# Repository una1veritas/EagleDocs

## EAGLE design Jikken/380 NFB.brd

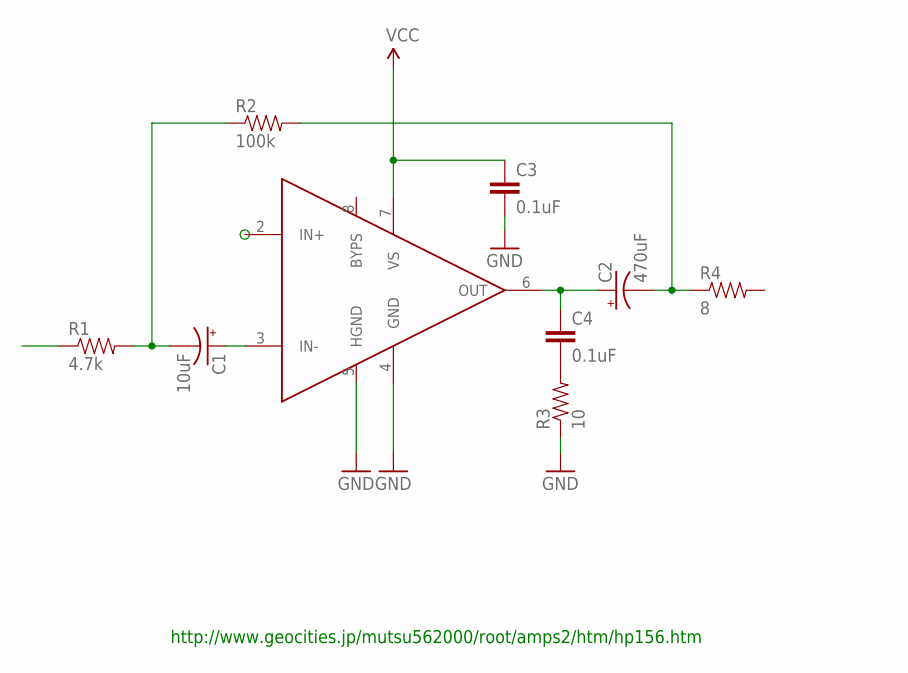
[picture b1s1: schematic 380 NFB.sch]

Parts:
C1: 10uF; CPOL-RADIAL-100UF-25V
C2: 470uF; CPOL-RADIAL-1000UF-25V
C3, C4: 0.1uF; CAP-PTH-SMALL-KIT
R1: 4.7k; AXIAL-0.3
R2: 100k; AXIAL-0.3
R3: 10; AXIAL-0.3
R4: 8; AXIAL-0.3
U$1: LM380N-8; DIL08

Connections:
GND: C3.2, R3.P$1 (1), U$1.4 (GND), U$1.5 (HGND)
unnamed: C1.1 (+), U$1.3 (IN-)
unnamed: C1.2 (-), R1.P$2 (2), R2.P$1 (1)
unnamed: C2.2 (-), R2.P$2 (2), R4.P$1 (1)
unnamed: C2.1 (+), C4.1, U$1.6 (OUT)
unnamed: C4.2, R3.P$2 (2)
VCC: C3.1, U$1.7 (VS)

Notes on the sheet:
http://www.geocities.jp/mutsu562000/root/amps2/htm/hp156.htm

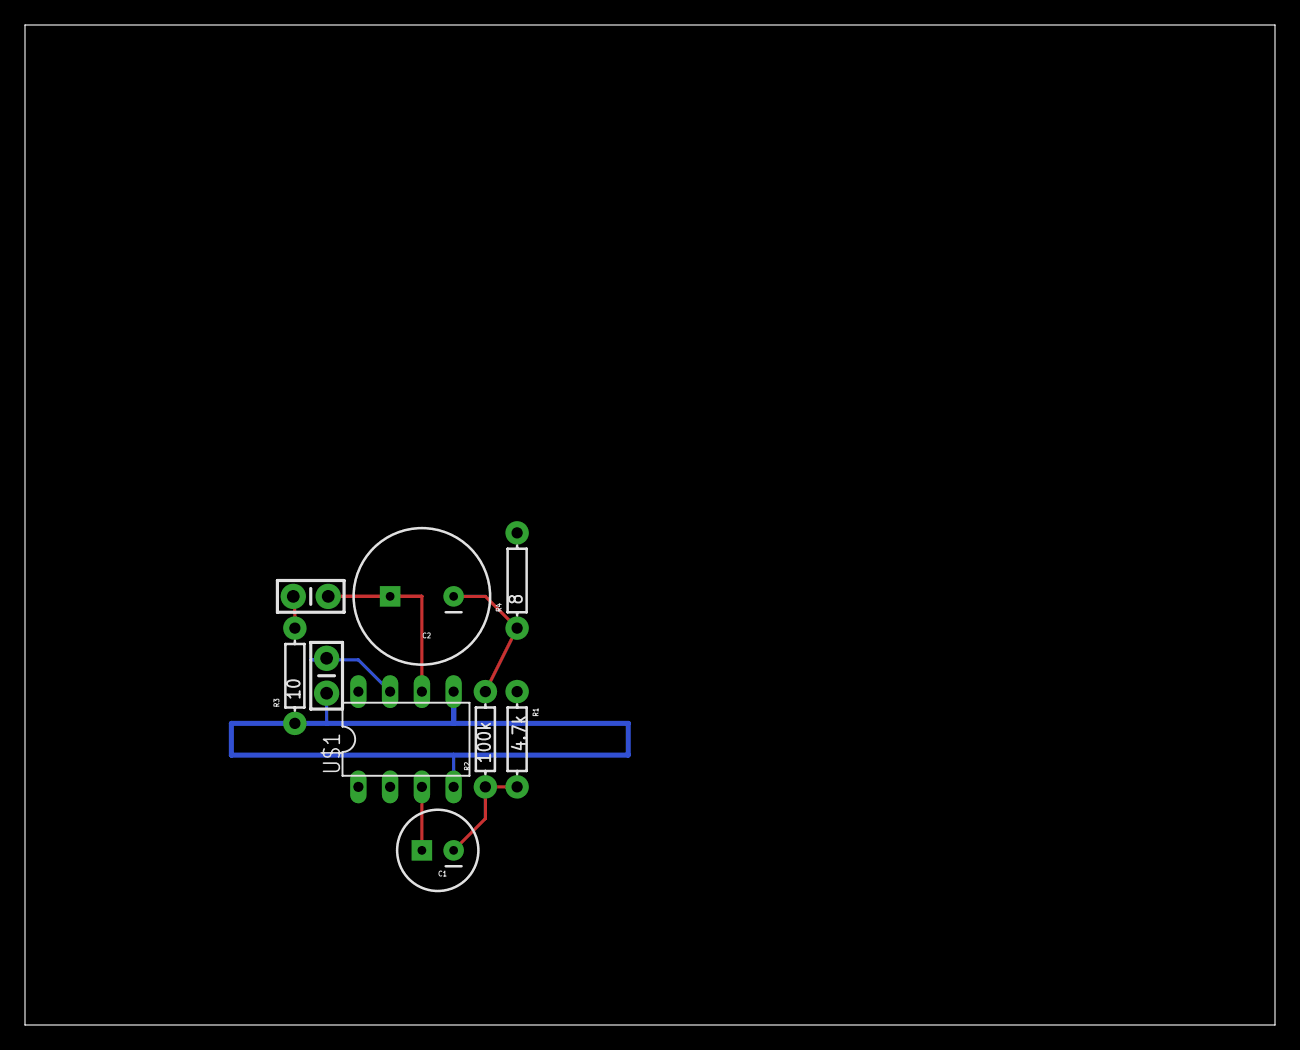
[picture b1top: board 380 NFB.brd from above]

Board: 2 copper layers, 100.0 x 80.0 mm, 9 parts (0 on the bottom side), 7 nets.

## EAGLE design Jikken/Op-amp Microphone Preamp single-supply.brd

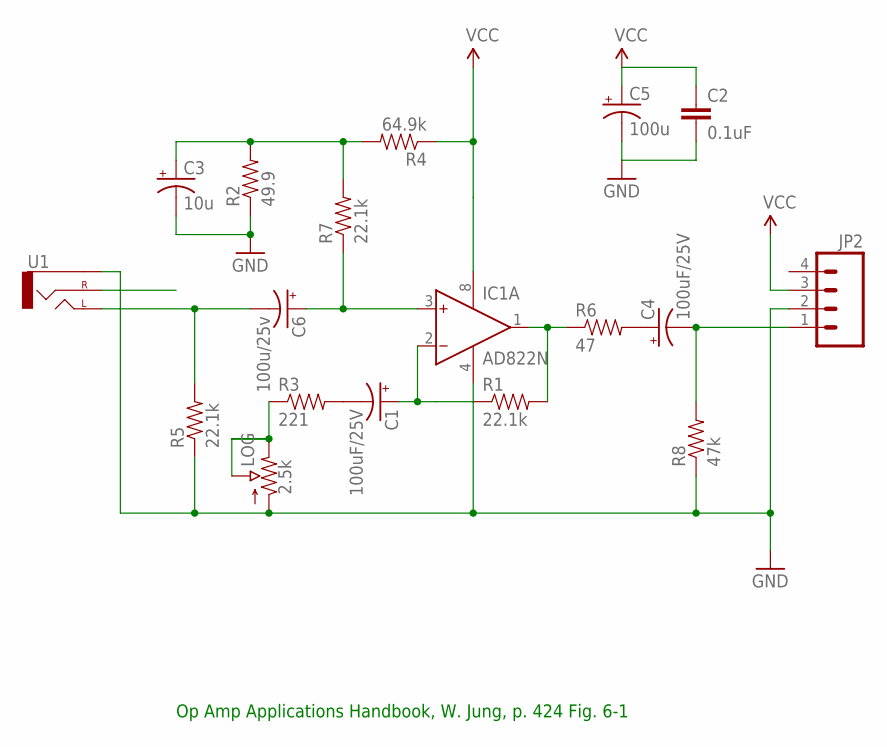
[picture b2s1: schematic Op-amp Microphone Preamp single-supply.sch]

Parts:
C1, C4: 100uF/25V; CPOL-RADIAL-100UF-25V
C2: 0.1uF; CAP-PTH-SMALL-KIT
C3: 10u; CPOL-RADIAL-100UF-25V
C5: 100u; CPOL-RADIAL-100UF-25V
C6: 100u/25v; CPOL-RADIAL-100UF-25V
IC1: AD822N; DIL08
JP2: M04POLAR; MOLEX-1X4
LOG: 2.5k; POT_ALPHA_RV16AF-20
R1, R5, R7: 22.1k; 1/6W-RES
R2: 49.9; 1/6W-RES
R3: 221; 1/6W-RES
R4: 64.9k; 1/6W-RES
R6: 47; 1/6W-RES
R8: 47k; 1/6W-RES
U1: AUDIO-JACKPTH; AUDIO-JACK

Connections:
GND: C2.2, C3.2 (-), C5.2 (-), IC1.4 (V-), JP2.2, LOG.1 (A), R2.1, R5.1, R8.1, U1.SLEEVE
unnamed: C3.1 (+), R2.2, R4.2, R7.2
unnamed: C1.2 (-), R3.2
unnamed: IC1.1 (OUT), R1.2, R6.1
unnamed: LOG.2 (S), LOG.3 (E), R3.1
unnamed: C1.1 (+), IC1.2 (IN-), R1.1
unnamed: C6.1 (+), IC1.3 (IN+), R7.1
unnamed: C4.1 (+), R6.2
unnamed: C6.2 (-), R5.2, U1.TIP (LEFT)
unnamed: C4.2 (-), JP2.1, R8.2
VCC: C2.1, C5.1 (+), IC1.8 (V+), JP2.3, R4.1

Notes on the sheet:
Op Amp Applications Handbook, W. Jung, p. 424 Fig. 6-1

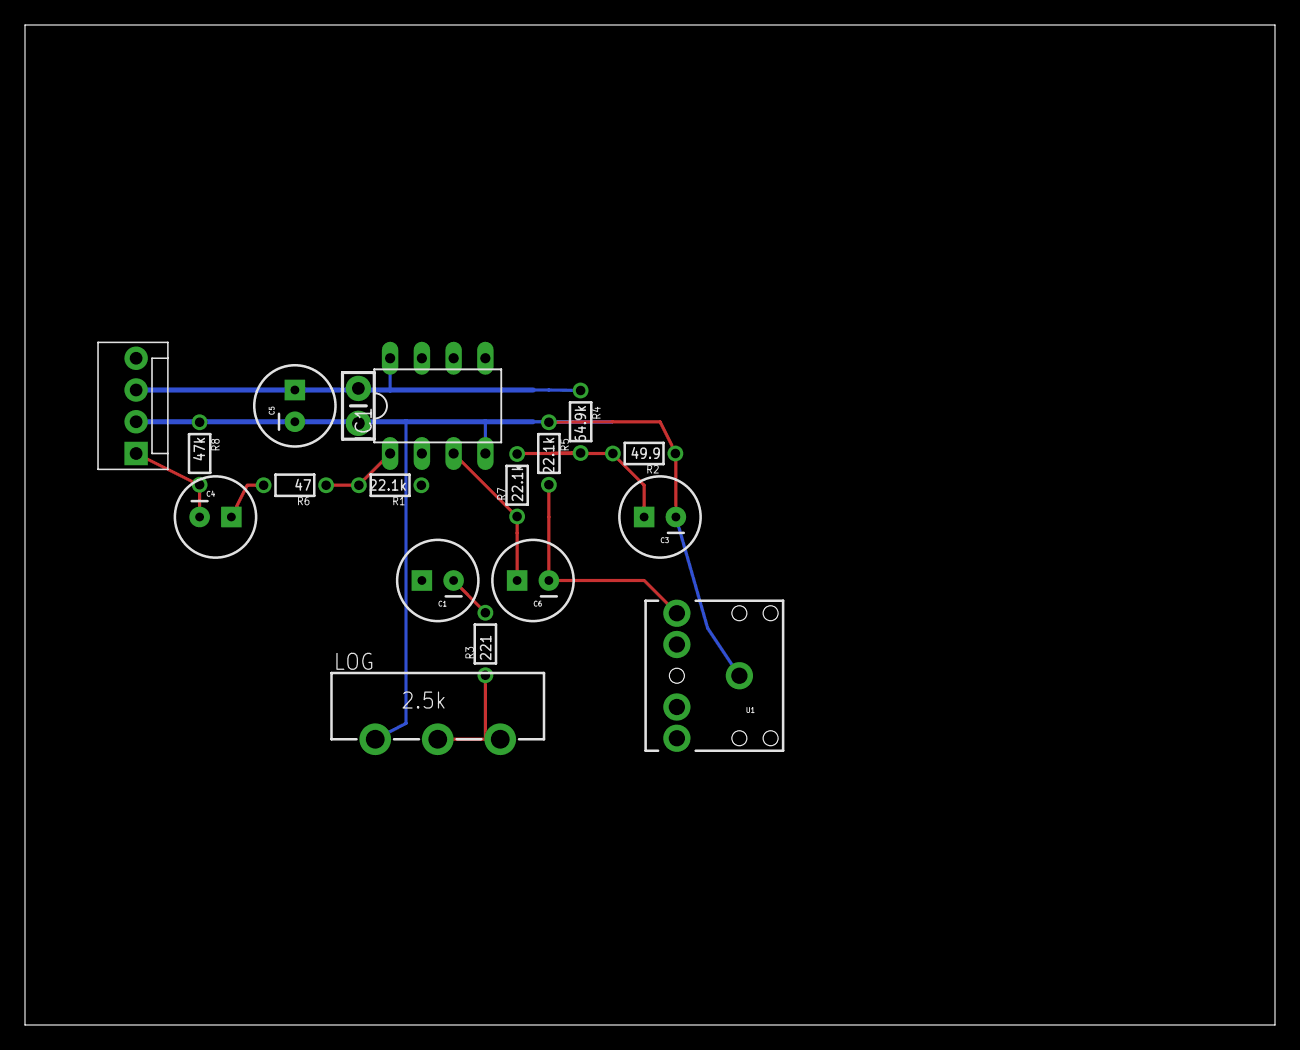
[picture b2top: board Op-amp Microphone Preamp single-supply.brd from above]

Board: 2 copper layers, 100.0 x 80.0 mm, 18 parts (0 on the bottom side), 11 nets.

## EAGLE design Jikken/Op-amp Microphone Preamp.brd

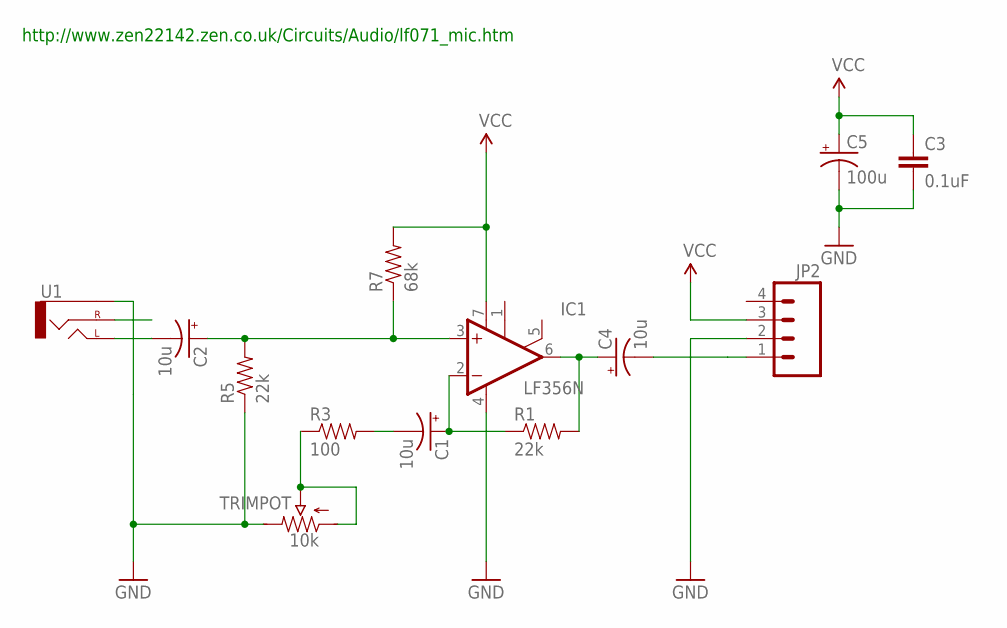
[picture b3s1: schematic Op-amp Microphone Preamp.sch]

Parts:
C1, C2, C4: 10u; CPOL-RADIAL-100UF-25V
C3: 0.1uF; CAP-PTH-SMALL
C5: 100u; CPOL-RADIAL-100UF-25V
IC1: LF356N; DIL08
JP2: M04POLAR; MOLEX-1X4
R1, R5: 22k; 1/6W-RES
R3: 100; 1/6W-RES
R7: 68k; 1/6W-RES
TRIMPOT: 10k; 3362U
U1: AUDIO-JACKPTH; AUDIO-JACK

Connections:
GND: C3.2, C5.2 (-), IC1.4 (V-), JP2.2, R5.1, TRIMPOT.P$1 (E), U1.SLEEVE
unnamed: C1.2 (-), R3.2
unnamed: C4.1 (+), IC1.6 (OUT), R1.2
unnamed: R3.1, TRIMPOT.P$2 (S), TRIMPOT.P$3 (A)
unnamed: C1.1 (+), IC1.2 (-IN), R1.1
unnamed: C2.1 (+), IC1.3 (+IN), R5.2, R7.1
unnamed: C2.2 (-), U1.TIP (LEFT)
unnamed: C4.2 (-), JP2.1
VCC: C3.1, C5.1 (+), IC1.7 (V+), JP2.3, R7.2

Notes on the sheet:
http://www.zen22142.zen.co.uk/Circuits/Audio/lf071_mic.htm

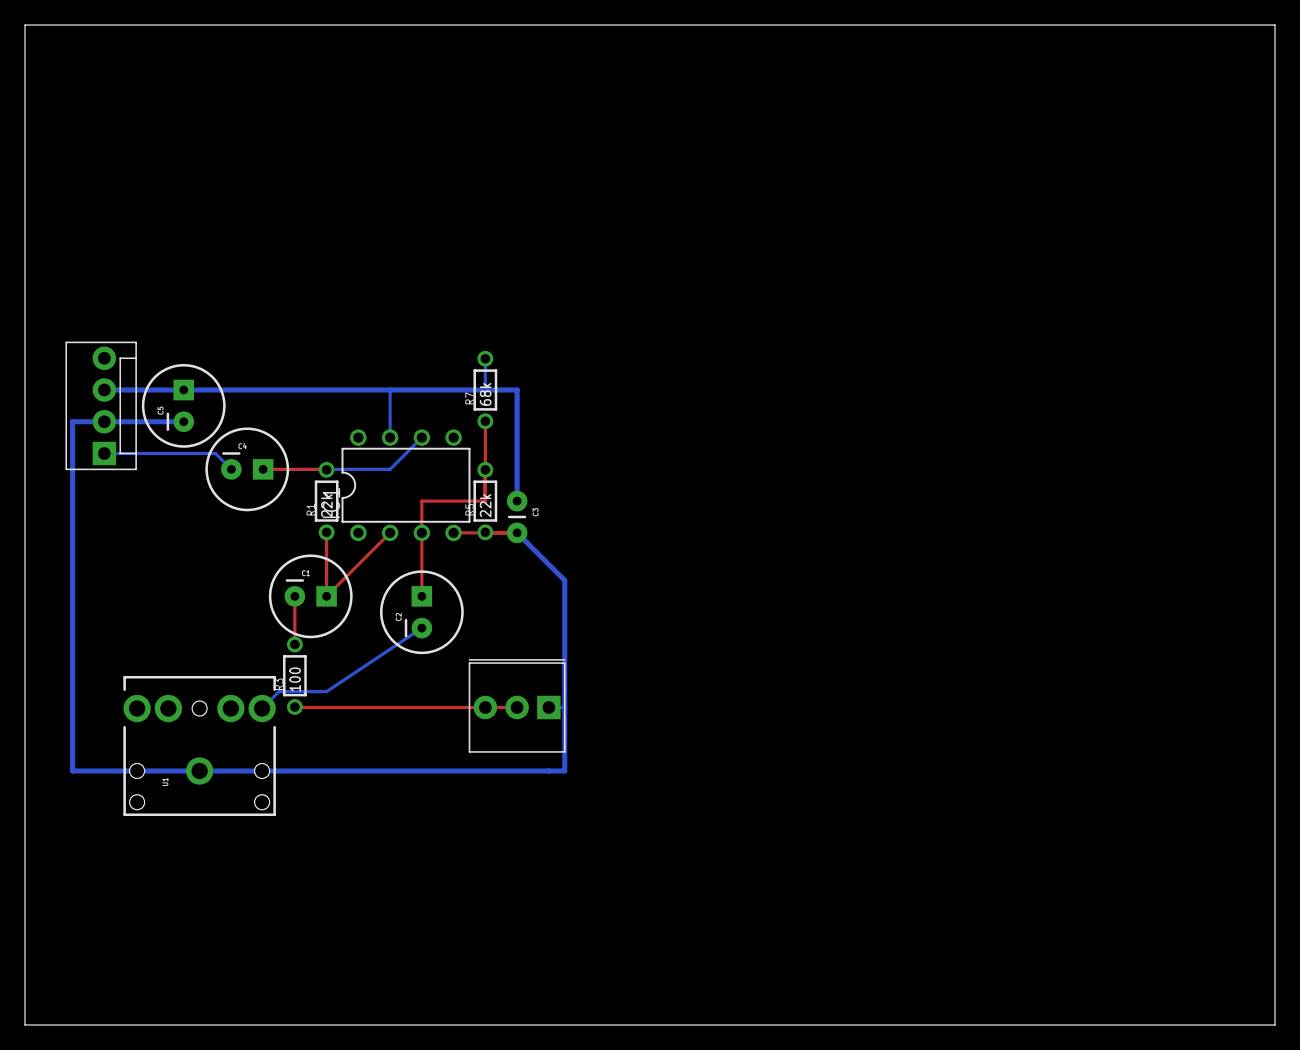
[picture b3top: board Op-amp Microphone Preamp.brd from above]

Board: 2 copper layers, 100.0 x 80.0 mm, 13 parts (0 on the bottom side), 9 nets.

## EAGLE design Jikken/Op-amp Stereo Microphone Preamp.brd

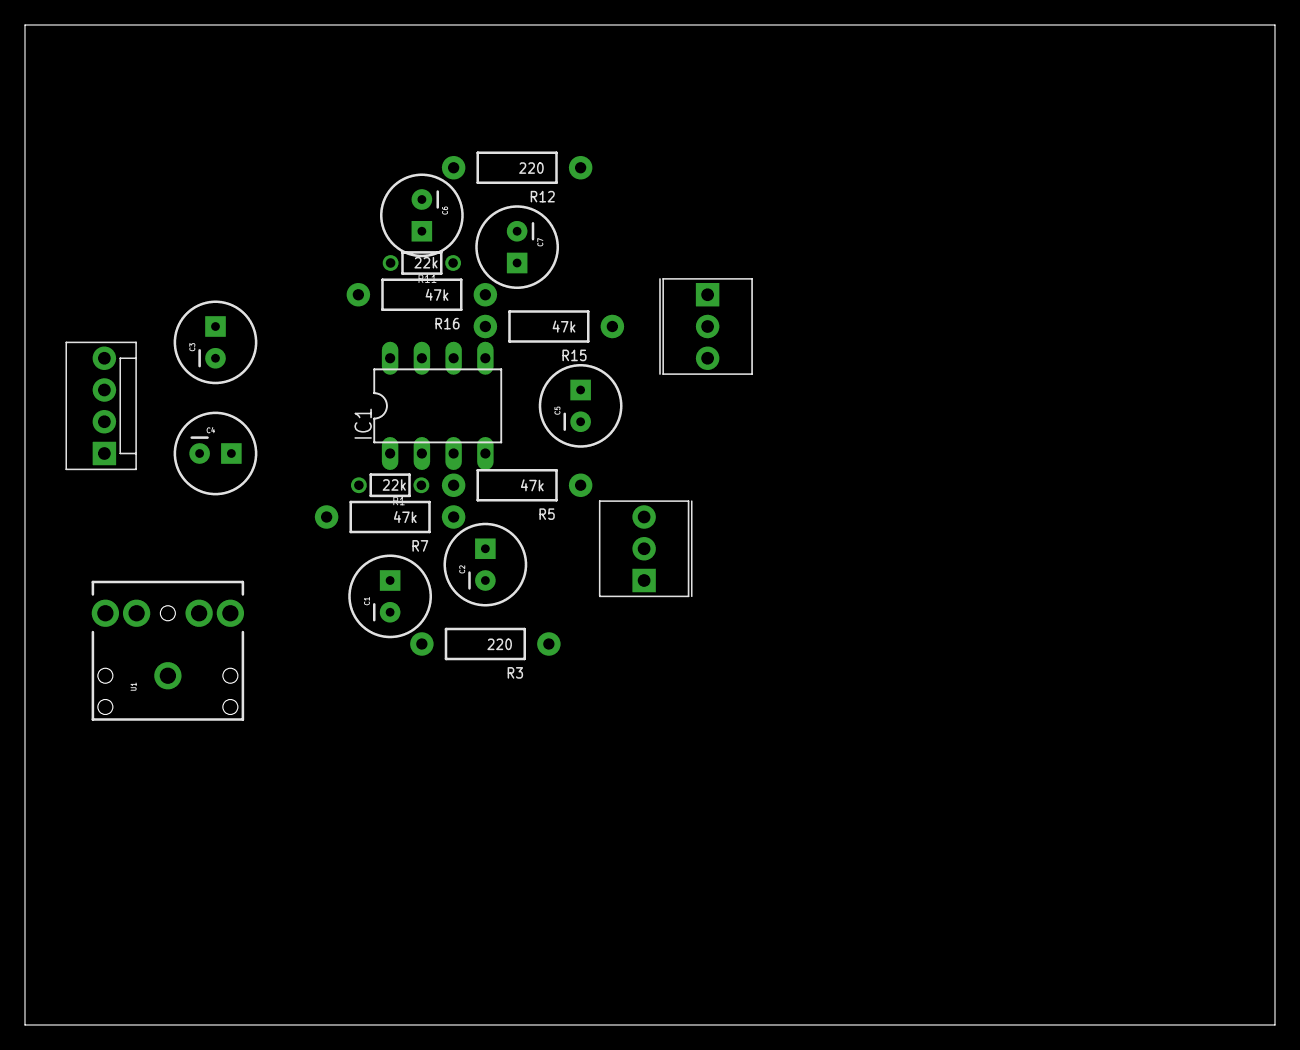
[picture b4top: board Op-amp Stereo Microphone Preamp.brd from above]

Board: 2 copper layers, 100.0 x 80.0 mm, 20 parts (0 on the bottom side), 16 nets, no tracks yet.

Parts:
C1, C2, C3, C4, C6, C7: 10u; CPOL-RADIAL-100UF-25V
C5: 100u; CPOL-RADIAL-100UF-25V
IC1: AD822N; DIL08
JP2: MOLEX-1X4
R1, R11: 22k; 1/6W-RES
R3, R12: 220; AXIAL-0.4
R5, R7, R15, R16: 47k; AXIAL-0.4
U1: AUDIO-JACK
U$1, U$2: 20k; 3362U

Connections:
GND: C5.2, IC1.4, JP2.2, R5.P$1, R15.P$1, U1.SLEEVE, U$1.P$3, U$2.P$3
unnamed: R3.P$1, U$1.P$1, U$1.P$2
unnamed: C1.2, R3.P$2
unnamed: C4.1, IC1.1, R1.2
unnamed: C3.2, JP2.4
unnamed: C1.1, IC1.2, R1.1
unnamed: C2.1, IC1.3, R5.P$2, R7.P$1
unnamed: C7.1, IC1.5, R15.P$2, R16.P$1
unnamed: C2.2, U1.TIP
unnamed: C7.2, U1.RING
unnamed: R12.P$1, U$2.P$1, U$2.P$2
unnamed: C6.2, R12.P$2
unnamed: C6.1, IC1.6, R11.1
unnamed: C4.2, JP2.1
unnamed: C3.1, IC1.7, R11.2
VCC: C5.1, IC1.8, JP2.3, R7.P$2, R16.P$2

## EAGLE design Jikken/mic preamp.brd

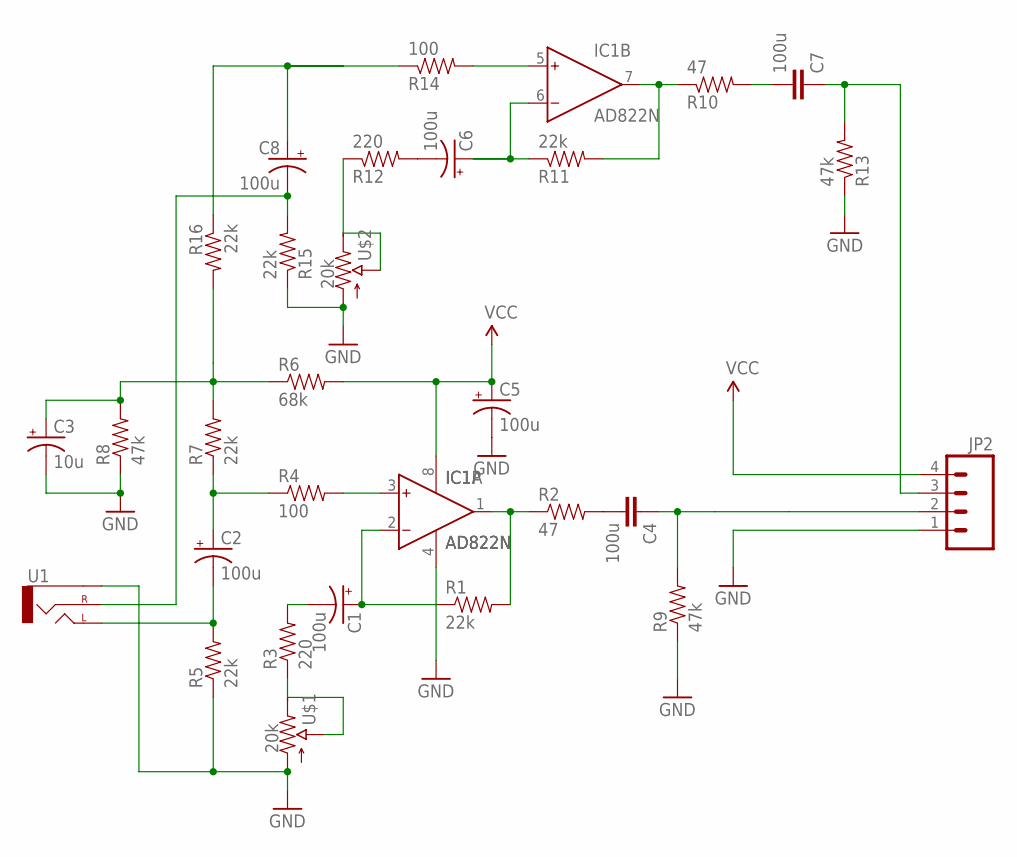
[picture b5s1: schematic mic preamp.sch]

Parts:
C1, C2, C5, C6, C8: 100u; CPOL-RADIAL-100UF-25V
C3: 10u; CPOL-RADIAL-100UF-25V
C4, C7: 100u; C2.5-4
IC1: AD822N; DIL08
JP2: M04POLAR; MOLEX-1X4
R1, R5, R11, R15: 22k; 1/6W-RES
R2, R10: 47; 1/6W-RES
R3, R12: 220; 1/6W-RES
R4, R14: 100; 1/6W-RES
R6: 68k; 1/6W-RES
R7, R16: 22k; AXIAL-0.3
R8, R9, R13: 47k; 1/6W-RES
U1: AUDIO-JACKPTH; AUDIO-JACK
U$1, U$2: 20k; POT_ALPHA_RV16AF-20

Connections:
GND: C3.2 (-), C5.2 (-), IC1.4 (V-), JP2.1, R5.1, R8.1, R9.1, R13.1, R15.1, U1.SLEEVE, U$1.1 (A), U$2.1 (A)
unnamed: R3.1, U$1.2 (S), U$1.3 (E)
unnamed: C1.2 (-), R3.2
unnamed: IC1.1 (OUT), R1.2, R2.1
unnamed: C4.2, R2.2
unnamed: C1.1 (+), IC1.2 (IN-), R1.1
unnamed: C2.2 (-), R5.2, U1.TIP (LEFT)
unnamed: C2.1 (+), R4.1, R7.P$1 (1)
unnamed: IC1.3 (IN+), R4.2
unnamed: C3.1 (+), R6.1, R7.P$2 (2), R8.2, R16.P$2 (2)
unnamed: R12.1, U$2.2 (S), U$2.3 (E)
unnamed: C6.2 (-), R12.2
unnamed: C6.1 (+), IC1.6 (IN-), R11.1
unnamed: C4.1, JP2.2, R9.2
unnamed: IC1.7 (OUT), R10.1, R11.2
unnamed: C8.2 (-), R15.2, U1.RING (RIGHT)
unnamed: C7.2, R10.2
unnamed: C7.1, JP2.3, R13.2
unnamed: C8.1 (+), R14.1, R16.P$1 (1)
unnamed: IC1.5 (IN+), R14.2
VCC: C5.1 (+), IC1.8 (V+), JP2.4, R6.2

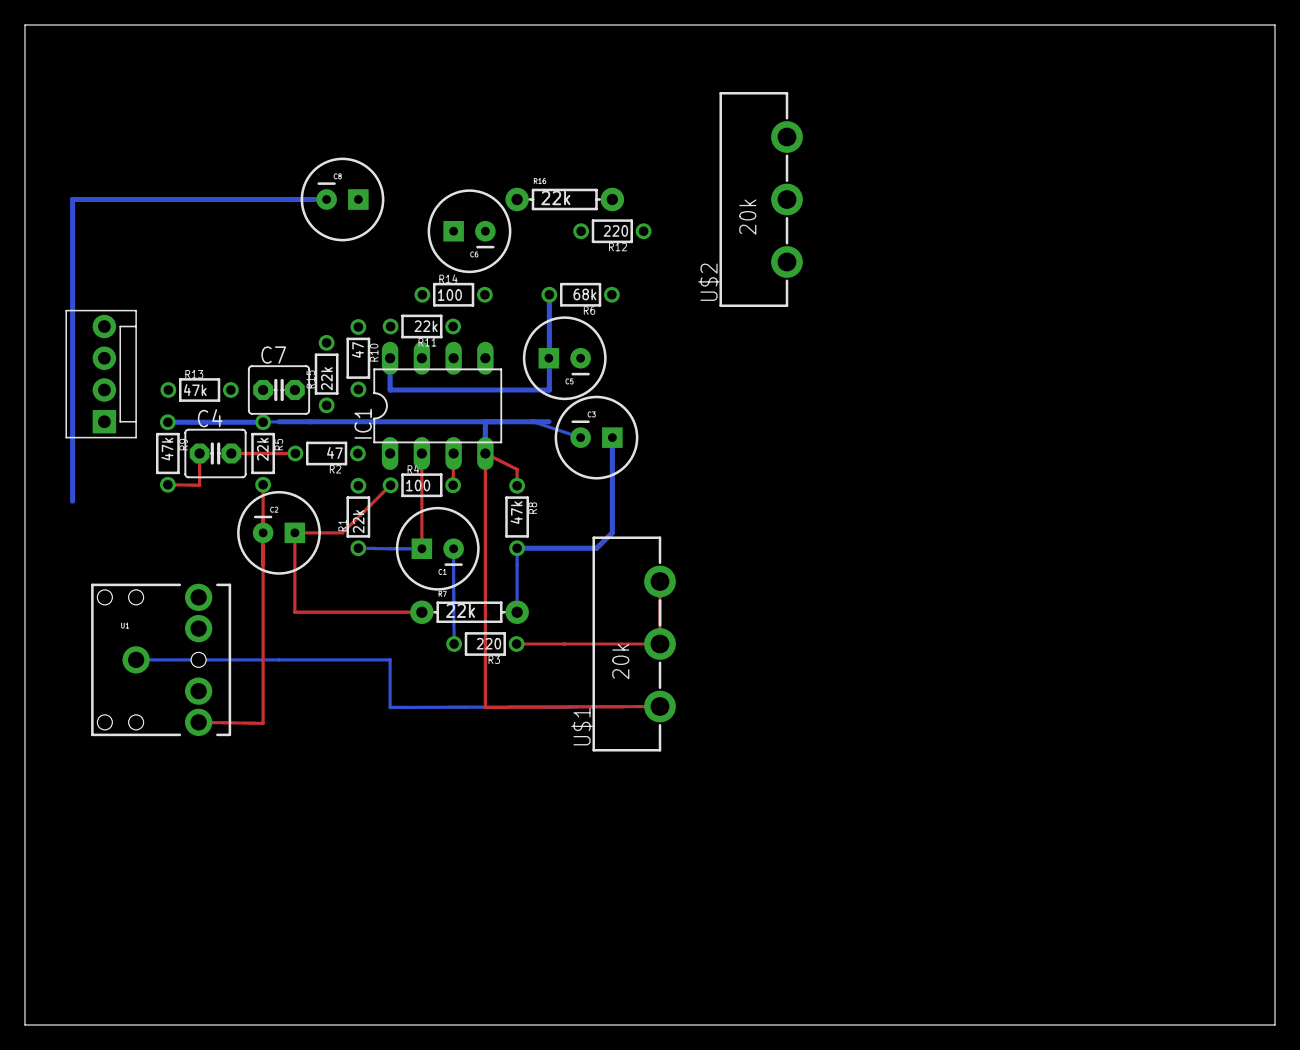
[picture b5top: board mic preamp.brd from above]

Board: 2 copper layers, 100.0 x 80.0 mm, 29 parts (0 on the bottom side), 21 nets.

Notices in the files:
parts and their libraries:
SparkFun: Licensing: CC v3.0 Share-Alike You are welcome to use this library for commercial purposes.
